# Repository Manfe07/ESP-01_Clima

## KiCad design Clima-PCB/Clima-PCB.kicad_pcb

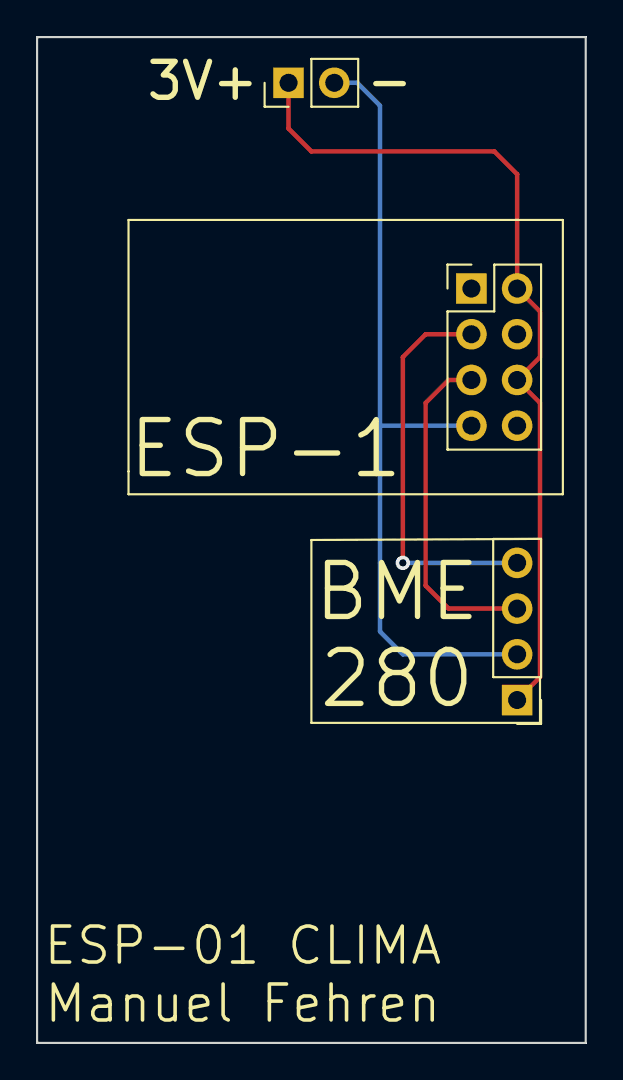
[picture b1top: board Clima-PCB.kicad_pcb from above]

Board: 2 copper layers, 30.5 x 55.9 mm, 3 parts (0 on the bottom side), 4 nets.

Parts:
3V+    -: Conn_01x02_Male; PinHeader_1x02_P2.54mm_Vertical
BME280: Conn_01x04_Female; PinHeader_1x04_P2.54mm_Vertical
ESP-1: Conn_02x04_Odd_Even; PinHeader_2x04_P2.54mm_Vertical

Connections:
+3V3: 3V+ -.1, BME280.1, ESP-1.2, ESP-1.6
GND: 3V+ -.2, BME280.2, ESP-1.7
SCL: BME280.3, ESP-1.5
SDA: BME280.4, ESP-1.3

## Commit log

2019-09-04 basic project
2019-09-04 added settings.h
2019-09-04 gitignore kicad
2019-09-04 created PCB
